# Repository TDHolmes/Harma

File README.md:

# Harma Project

The Harma project first came about when I was talking to my friend and coworker Ben. We are both tinkerers and He used to work as a rework technician, so is quite good at fine pitch soldering. I however, have very shaky hands, so I shy away from anything smaller than an 0805 passive component.

That got me thinking, there are robotic assistants for surgeries, so why not for an over caffeinated tinkerer like myself?

Thus, this project was born. It consists of two major parts:

1. The thing the tinkerer holds on to to control the robot
2. The robotic arms holding:
   * The soldering iron
   * The solder
   * The wire or component

### The Name

Harma comes from the word Härma, which means Mimic in Swedish. A fitting name since the goal of this project is for you to control a robot that mimics your movements in a more precise and filtered way.

## Sub-Components

As stated above, this project consists of two major parts: The thing the user holds to control the robot and the robotic arms itself.

### [Pensel][Pensel Link]

Pensel, or brush/pencil in Swedish, is the device the user interfaces with to control the robotic arms. It is this sub-component that I will first tackle to make the whole system. The design as it stands is as follows:

There will be one unified design to control the iron, solder, and/or wire/components. As such, there must be a generic control methodology built into the Pensel. The Pensel will have:

1. A three position toggle switch for the user to indicate what mode the Pensel is operating in (Soldering iron, solder, or wire/component).
2. One push button to indicate that we are actively moving and want the robot to respond
3. Another push button to do the action supported by the mode. For example:
   * Feed solder
   * Feed wire
   * release component

Further Pensel documentation can be found [here][Pensel Link].

#### The Current design

* Processor
   * STM32F302K8U6
   * ARM® Cortex®-M4
   * 72MHz
   * CAN, I²C, IrDA, LIN, SPI, UART/USART, USB
   * DMA, I²S, POR, PWM, WDT
   * Hardware FPU
* Sensors
   * Combined Accelerometer and Magnetometer (LSM303DLHC) to detect orientation & movement
   * A button to trigger "active" mode
   * An auxiliary button to generate an action
   * A three position switch to indicate the active mode
   * A thumbwheel potentiometer to control sensitivity

### Robotic Arms (Working title)

This section has not been thought through yet. I am currently only focusing on the Pensel sub-component.

[Pensel Link]: https://www.holmesengineering.com/Harma/Pensel "Pensel Sub-Project Page"

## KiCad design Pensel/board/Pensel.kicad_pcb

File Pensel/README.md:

# Pensel

Pensel, or brush/pencil in Swedish, is the device the user interfaces with to control
the robotic arms. It is this sub-component that I will first tackle to make the whole
system. The design as it stands is as follows:

There will be one unified design to control the iron, solder, and/or wire/components.
As such, there must be a generic control methodology built into the Pensel. The
Pensel will have as follows:

1. A three position toggle switch for the user to indicate what mode the Pensel is
operating in (Soldering iron, solder, or wire/component).
2. One push button to indicate that we are actively moving and want the robot to respond
3. Another push button to do the action supported by the mode. For example:
   * Feed solder
   * Feed wire
   * release component

## Hardware Basics

* STM32F302K8U6
  * ARM® Cortex®-M4 (with FPU)
  * I²C, UART/USART, USB, DMA, PWM, WDT
  * 72MHz
* Orientation / motion sensor for orientation and movement detection
  * LSM303DLHC accelerometer and magnetometer for version 1
  * LSM9DS1 accelerometer, magnetometer and gyroscope for version 2

### Pensel v1

![alt text][v1 Board Top]

#### Sensors

Pensel v1 utilized the now obsolete LSM303DLHC, an accelerometer/magnetometer
orientation sensor. I was hoping to achieve absolute orientation sensing with the
gravity vector and magnetic north vector. This is, however, very difficult with
magnetometer data, as it is very noisy and susceptible to local perturbations.

![alt text][v1 Mag Plot]

The accelerometer data, however, looked very promising.

![alt text][v1 Accel Plot]

#### Communication

The communication method was also less than ideal in v1. I utilized a USB to serial
converter chip to provide easy communication to the host, however to accommodate the
high data-rate sensors and have a general purpose report get/set architecture, I
basically re-implemented a USB HID device over serial, which doesn't make much sense.

![alt text][v1 comms]

### Pensel v2

![alt text][v2 Board Top]

Pensel v2 aims to rectify the issues with v1 by using a more robust, in production
accelerometer, magnetometer, and gyroscope sensor, the LSM9DS1. It also will
eliminate the USB to serial converter in favor of a direct USB connection and a
custom HID USB device. It is also my first adventure into four layer boards, which
made routing a dream.

#### Current Progress

I am currently working on getting the USB stack up and working. I found that I
forgot the 1.5k pull-up resistor on the D+ pin of the USB connection, which is
required to indicate device speed and device attachment. I have attached a bodge
wire to the D+ net (luckily I had pads for filter capacitors in case they were
needed) and am working on soldering some 0805 resistors to that line.

## Initial Software Design

Below is an overview of all of the modules in the system. This is only an initial
cut at the system and is subject to change.

![alt text][Software Diagram]

Below is an overview of the control and call structure of the system.

![alt text][Control Diagram]

[Software Diagram]: https://raw.githubusercontent.com/TDHolmes/Harma/master/Pensel/documentation/pictures/Pensel_SoftwareDiagram.png "Overall Pensel software diagram"
[Control Diagram]: https://raw.githubusercontent.com/TDHolmes/Harma/master/Pensel/documentation/pictures/Pensel_ControlHierarchy.png "Pensel control flow"

[v1 Board Top]: https://github.com/TDHolmes/Harma/blob/gh-pages/Pensel/documentation/pictures/Pensel_1_0_top.jpg?raw=true "Pensel v1 - Top"
[v1 Board Bottom]: https://github.com/TDHolmes/Harma/blob/gh-pages/Pensel/documentation/pictures/Pensel_1_0_bottom.jpg?raw=true "Pensel v1 - Bottom"

[v1 Accel Plot]: https://github.com/TDHolmes/Harma/blob/gh-pages/Pensel/Documentation/pictures/P1_HalfRotation_accel.png?raw=true "Accel plot of a half rotation of the unit"
[v1 Mag Plot]: https://github.com/TDHolmes/Harma/blob/gh-pages/Pensel/Documentation/pictures/P1_magRotation.png?raw=true "Magnetometer plot of a full Pensel rotation"
[v1 comms]: https://github.com/TDHolmes/Harma/blob/master/Pensel/Documentation/P1_UART_coms.png?raw=true "Pensel v1 UART packet definition"

[v2 Board Top]: https://github.com/TDHolmes/Harma/blob/master/Pensel/Documentation/pictures/Pensel_v2_Top.jpg?raw=true "Pensel v2 - Top"

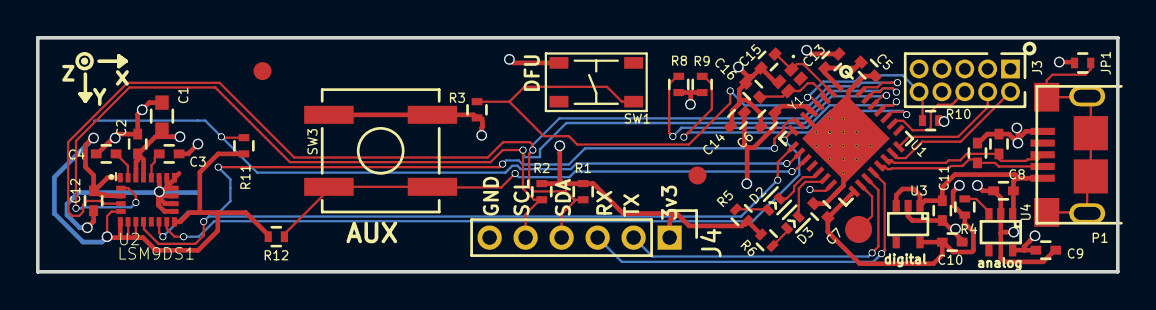
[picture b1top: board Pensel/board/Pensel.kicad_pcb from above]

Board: 4 copper layers, 60.0 x 13.0 mm, 48 parts (1 on the bottom side), 33 nets.

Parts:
C1: 10 uF; C_0603
C2, C4, C6, C7, C12, C13: 0.1 uF; C_0402
C3: 10 nF; C_0402
C5: 4.7 uF; C_0402
C8, C9, C10, C11, C14: 1 uF; C_0402
C15, C16: 8 pF; C_0402
C_NOSTUFF1, C_NOSTUFF2: 0.1 uF; C_0402
D2: LED0; LED_0402
D3: LED1; LED_0402
J1: TEST_1P; Measurement_Point_Round-SMD-Pad_Small
J2, J5: Fiducial; Fiducial_1mm_Dia_2.54mm_Outer_CopperBottom
J3: JTAG; Pin_Header_Straight_2x05_Pitch1.27mm
J4: COMS; Pin_Header_Straight_1x06_Pitch2.00mm
J6, J7: Fiducial; Fiducial_1mm_Dia_2.54mm_Outer_CopperTop
JP1: Jumper; R_0402
P1: USB_PROC; 2013499-1
R1, R2, R3, R4, R8, R9, R10, R11, R12: 4K7; R_0402
R5, R6: 330R; R_0402
SW1: TACT_4.2MM; MF_Switches-TACT4.2MM
SW2: MAIN; SW_SPST_B3SL-1002P
SW3: AUX; SW_SPST_B3SL-1002P
U1: STM32F302x6/8; QFN-32-1EP_5x5mm_Pitch0.5mm
U2: LSM9DS1; PQFN24P43_350X300X102L35X23N
U3: NCP114; SC-70-5
U4: NCP508; SC-70-5
Y1: 24 MHz; OSCSC49P160X120X45-4N

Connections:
+3.3VA: C1.1, C2.1, C6.1, C9.1, C14.1, U1.5, U2.22, U2.23, U4.5
+3V3: C5.1, C7.1, C10.1, C12.1, C13.1, J3.1, J4.1, R1.1, R2.1, R4.2, R5.1, R6.1, R10.1, R11.1, R12.1, SW1.1, U1.1, U1.17, U2.1, U2.3, U2.5, U2.6, U2.7, U2.8, U2.13, U3.5
+5V: C8.1, C11.1, P1.1, U3.1, U3.3, U4.1
/USB+: C_NOSTUFF1.2, P1.3, U1.22
/USB-: C_NOSTUFF2.1, P1.2, U1.21
/test_pin: J1.1, U1.18
AG_INT1: U1.7, U2.11
AG_INT2: U1.8, U2.12
BREV-0: R9.1, U1.27
BREV-1: R8.1, U1.28
BTN_AUX: R12.2, SW3.2, U1.11
BTN_MAIN: R11.2, SW2.2, U1.10
GND: C1.2, C2.2, C3.2, C4.2, C5.2, C6.2, C7.2, C8.2, C9.2, C10.2, C11.2, C12.2, C13.2, C14.2, C15.2, C16.2, C_NOSTUFF1.1, C_NOSTUFF2.2, J3.3, J3.5, J3.9, J4.6, JP1.1, P1.5, R3.2, R8.2, R9.2, SW2.1, SW3.1, U1.6, U1.16, U1.32, U1.33, U2.14, U2.15, U2.16, U2.17, U2.18, U2.19, U2.20, U3.2, U4.2, Y1.2
LED0: D2.1, U1.13
LED1: D3.1, U1.14
M_DRDY: U1.9, U2.9
unnamed: C3.1, U2.21
unnamed: C4.1, U2.24
unnamed: C15.1, U1.2, Y1.1
unnamed: C16.1, U1.3, Y1.3
unnamed: D2.2, R5.2
unnamed: D3.2, R6.2
unnamed: JP1.2, P1.6
unnamed: R3.1, SW1.4, U1.31
unnamed: R4.1, U4.3
RESET_n: J3.10, R10.2, U1.4
SCL: J4.5, R2.2, U1.29, U2.2
SDA: J4.4, R1.2, U1.30, U2.4
SWD-SWCLK: J3.4, U1.24
SWD-SWO: J3.6, U1.26
SWDIO: J3.2, U1.23
UART_RX: J4.3, U1.20
UART_TX: J4.2, U1.19

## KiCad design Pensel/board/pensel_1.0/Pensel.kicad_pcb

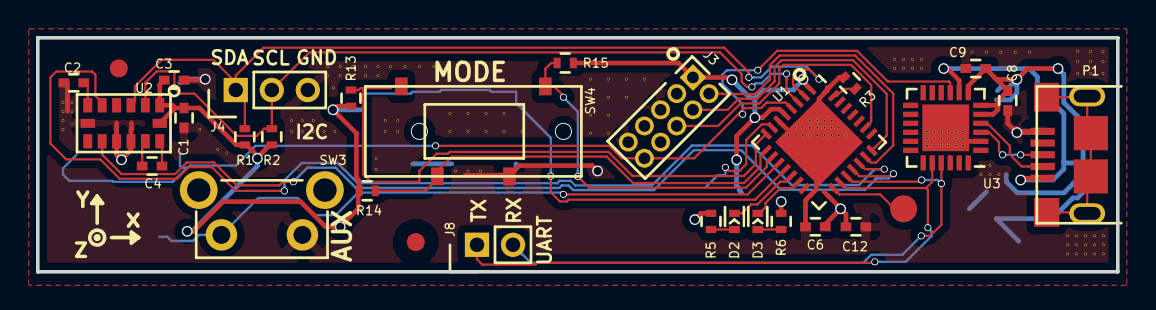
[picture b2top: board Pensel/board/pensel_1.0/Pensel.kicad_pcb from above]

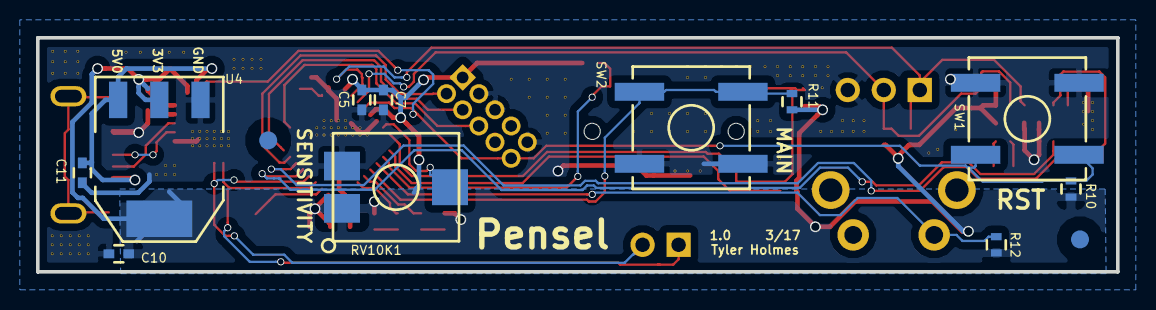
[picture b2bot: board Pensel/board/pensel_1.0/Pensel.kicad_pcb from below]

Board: 2 copper layers, 60.0 x 13.0 mm, 43 parts (11 on the bottom side), 30 nets.

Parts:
C1, C2, C5, C8: 4.7 uF; C_0402
C3, C6, C9, C12: 0.1 uF; C_0402
C4: 0.22 uF; C_0402
C7, C10, C11: 1 uF; C_0402
D2: LED0; LED_0402
D3: LED1; LED_0402
J1: TEST_1P; Measurement_Point_Round-SMD-Pad_Small
J2, J5: Fiducial; Fiducial_1mm_Dia_2.54mm_Outer_CopperBottom
J3: JTAG; Pin_Header_Straight_2x05_Pitch1.27mm
J4: I2C; Pin_Header_Straight_1x03_Pitch2.00mm
J6, J7: Fiducial; Fiducial_1mm_Dia_2.54mm_Outer_CopperTop
J8: UART; Pin_Header_Straight_1x02_Pitch2.00mm
P1: USB_PROC; 2013499-1
R1, R2, R3, R10, R11, R12, R13, R14, R15: 4K7; R_0402
R5, R6: 330R; R_0402
RV10K1: THUMBWHEEL; ST-4
SW1: RST; SW_SPST_B3SL-1002P
SW2: MAIN; SW_SPST_B3SL-1002P
SW3: AUX; SW_Tactile_SPST_Angled
SW4: MODE_SEL; CL-SB-13B-01
U1: STM32F302x6/8; QFN-32-1EP_5x5mm_Pitch0.5mm
U2: LSM303DLHC; LGA_14L_3mm_5mm
U3: CP2102N-A01-GQFN24; QFN-24-1EP_4x4mm_Pitch0.5mm
U4: AP111733; SOT-223

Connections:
+3V3: C1.1, C3.1, C5.1, C6.1, C7.1, C8.1, C9.1, C10.1, C12.1, J3.1, R1.1, R2.1, R5.1, R6.1, R10.1, R11.1, R12.1, R13.1, R14.1, R15.2, RV10K1.1, U1.1, U1.5, U1.17, U2.1, U2.14, U3.5, U3.6, U3.7, U4.2, U4.4
+5V: C11.1, P1.1, U3.8, U4.3
BTN_AUX: R12.2, SW3.2, U1.11
BTN_MAIN: R11.2, SW2.2, U1.12
DBG_UART_RX: J8.2, U1.20, U3.21
DBG_UART_TX: J8.1, U1.19, U3.20
GND: C1.2, C2.2, C3.2, C5.2, C6.2, C7.2, C8.2, C9.2, C10.2, C11.2, C12.2, J3.3, J3.5, J3.9, J4.3, P1.5, R3.2, RV10K1.3, SW1.1, SW2.1, SW3.1, SW4.3, U1.6, U1.16, U1.32, U1.33, U2.7, U2.10, U2.11, U3.2, U3.25, U4.1
LED0: D2.1, U1.13
LED1: D3.1, U1.14
MODE_0: R13.2, SW4.1, U1.8
MODE_1: R14.2, SW4.2, U1.9
MODE_2: R15.1, SW4.4, U1.10
unnamed: C2.1, U2.6
unnamed: C4.1, U2.13
unnamed: C4.2, U2.12
unnamed: D2.2, R5.2
unnamed: D3.2, R6.2
unnamed: J1.1, U1.18
unnamed: P1.2, U3.4
unnamed: P1.3, U3.3
unnamed: R3.1, U1.31
RESET_n: J3.10, R10.2, SW1.2, U1.4, U3.9
SCL: J4.2, R2.2, U1.3, U2.2
SDA: J4.1, R1.2, U1.2, U2.3
SEN_DRDY: U1.21, U2.9
SEN_INT1: U1.22, U2.5
SWD-SWCLK: J3.4, U1.24
SWD-SWO: J3.6, U1.26
SWDIO: J3.2, U1.23
THUMBWHEEL: RV10K1.2, U1.7

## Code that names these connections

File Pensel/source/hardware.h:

#ifndef _HARDWARE_H_
#define _HARDWARE_H_


#include "stm32f3xx.h"

// Sensor stuff
#define SENSOR_PORT (GPIOA)
#define SENSOR_DRDY (GPIO_PIN_11)
#define SENSOR_INT  (GPIO_PIN_12)

// LED / exposed pad stuff
#define LED_PORT   (GPIOA)
#define LED_0      (GPIO_PIN_6)
#define LED_1      (GPIO_PIN_7)
#define EXTRA_GPIO (GPIO_PIN_8)

// Button & switch stuff
#define SWITCH_BUTTON_PORT (GPIOA)
#define BUTTON_MAIN        (GPIO_PIN_5)
#define BUTTON_AUX         (GPIO_PIN_4)
#define SWITCH_0           (GPIO_PIN_1)
#define SWITCH_1           (GPIO_PIN_2)
#define SWITCH_2           (GPIO_PIN_3)

// Thumbwheel
#define THUMBWHEEL_PORT (GPIOA)
#define THUMBWHEEL      (GPIO_PIN_0)

// I2C
#define I2C_PORT    (GPIOF)
#define I2C_SDA     (GPIO_PIN_0)
#define I2C_SCL     (GPIO_PIN_1)

// UART
#define UART_PORT   (GPIOA)
#define UART_RX     (GPIO_PIN_10)
#define UART_TX     (GPIO_PIN_9)


// Public function definitions
void SystemClock_Config(void);
void configure_pins(void);

void LED_toggle(uint16_t LED);
void LED_set(uint16_t LED, uint8_t value);


#endif /* _HARDWARE_H_ */

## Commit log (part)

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2017-03-11 adding in sub-folder for Pensel sub component
2017-03-12 adding in PinAllocations spreadsheet
2017-03-12 First revision of pinout complete
2017-03-13 fixing formatting issues and adding some more inof
2017-03-13 stubbing out I2C functions required
2017-03-13 adding in common header for ret_t retval enumeration
2017-03-13 adding explicit cast to int16_t
2017-03-15 Initial schematic placement
2017-03-15 Placement of major components
2017-03-15 most of the major wiring
2017-03-16 adding in processor ref manual
2017-03-16 adding STM HAL files
2017-03-19 moved datasheets into folder and added FTDI and accel
2017-03-26 adding .kicad_pcb-bak to gitignore
2017-03-26 gerber output of first complete route
2017-03-26 fixing output folder and contents for gerber files
2017-04-02 switched to LSM303DLHC accel and gyro only and did first cut at ull route
2017-04-08 final modifications and gerber export for v1_0 sent to macrofab
2017-04-22 removing STM_drivers folder in favor of a peared down drivers folder
2017-04-22 initial cut at UART using HAL
2017-04-22 adding required libraries
2017-04-22 adding linker file
2017-04-22 adding in a hardware file for hardware specific functions
2017-04-22 fixing up my files so they're HAL complient
2017-04-22 first successful build of the project
2017-04-22 added a UART_isReady() function to see if UART tx is busy
2017-04-24 adding stupid catchall RET_GEN_ERR to ret_t type
2017-04-29 adding queues to the sensor for easy getting from app code
2017-04-29 adding -g to release flags so we can debug
2017-04-29 adding interrupt for sensor and configuring priorities
2017-04-29 adding .elf files to ignor
2017-04-29 adding helloWorld UART in main loop and an implementation of the HAL_IncTick function for 1ms ISR to call other functions that need periodic updating
2017-04-30 switching CRLF to LF
2017-04-30 switching to LF to CRLF
2017-05-01 implementing the interrupt prioritization as well as documenting it
2017-05-01 fixing linker script name and adding a check if folders exist. if not, make it
2017-05-05 the start of reports structure
2017-05-05 moving queue_t to queue.h
2017-05-05 adding a peakChar function
2017-05-06 getting UART to work properly
2017-05-06 fixing up hal config file
2017-05-06 adding GDB startup script and moving build script to scripts folder
2017-05-06 some debug main loop things for board bringup
2017-05-14 removing unused code for different chip
2017-05-14 adding parser scripts for UART data and recorded data for offline playback
2017-05-14 Making I2C work
2017-05-14 Switching SystemClock_Config to a different example
2017-05-14 making fatal_error_handler print file and line number of error and adding some return types
2017-05-14 cleaning up and making LSM303DLHC code work
2017-05-15 fimrware folder re-organize
2017-05-17 adding more description to the GDB startup python script
2017-05-17 adding in normalization code and switching accel and mag datatypes to float
2017-05-17 adding functions to toggle the extra timing GPIO
2017-05-17 removing the deleted cli.c/h files
2017-05-21 adding tests for newqueue and improving other tests
2017-05-21 adding/fixing doxygen comments
2017-05-21 fixing build script per reorg and made it prettier
2017-05-21 switching scripts over to floating point
2017-05-21 increasing heap size and adding some optional linker flags
2017-05-21 switching to reflect changes in report module and LSM sensor packet changes
2017-05-22 documenting UART methods and cleaning up
2017-05-22 slight adjustments
2017-05-22 adding more queue tests
2017-05-25 Adding watchdog support
2017-06-03 Adding timeouts and magic numbers
    Reports will now timeout after "RPT_TIMEOUT" time.
    Reports also must now start with two magic bytes, 0xBE and 0xEF to signify
    the start of a report to avoid corrupt reports and getting out of sync.
    :
2017-06-03 addinng UNUSED_PARAM macro and RET_NOMEM_ERR when malloc is involved
2017-06-03 interrupt handlers now end with _ISR
2017-06-03 removing .h files from add_executable source list
2017-06-03 adding FIR support as well as some coefficients
2017-06-03 initial add for quanternion support
2017-06-03 initial add of the orientation module
    This module will be responsible for:
    1. Calculating gravity vector orientation
    2. Calculating North vector orientation
    3. Using (1) and (2) to calculate Pensel's orientation
2017-06-03 Adding a draw.io UML diagram of an overview of the blocks of the system
    This is a great high level visualization of low level drivers leading up to
    high level blocks that crank on the data and do the real work.
2017-06-03 updating project info as some things have changed
2017-06-04 Moving HAL specific configuration code to DriverConf folder
    This is mainly to avoid getting all of the HAL configuration code included in the
    doxygen firmware documentation. Super annoying... the PDF becomes 1300 pages long
    with all of the driver documentation!
2017-06-04 adding better support for doxygen PDF generation
2017-06-04 removing unnecessary definition
2017-06-04 making orientation compile in
2017-06-04 changing to signed datatypes in two for loops as we have a >= 0 conditional
2017-06-12 adding static declarations where applicable and adding some docs
2017-06-12 initial layout of the gh-pages
2017-06-12 fixing up documentation
2017-06-12 fixing format error
2017-06-12 adding firmware documentation
2017-06-12 fixing format
2017-06-12 making Pensel documentation link absolute
2017-06-12 adding http redirect
2017-06-25 making LED_set make logical sense given the active low LED config and fixing hardware dependencies
2017-06-25 minor cleanup and tweaking temperature report
2017-06-25 adding python script to send reports
2017-06-25 adding frame_num to accel and mag packets
2017-06-25 some more minor reports
2017-06-25 updated pensel docs with pixtures
2017-06-25 consolidating and renaming the coefficients files
2017-06-25 cleaning up FIR and added a testcase for the FIR filter
2017-06-26 adding schematic PDF and timing analysis pictures
2017-06-26 fixing normalization of vector
2017-06-26 fixing timing pin declaration
2017-06-26 getting plot sensor data script to work with new reports
2017-06-26 consolidating FIR_coefficients filename change
2017-06-26 Changing mag sensitivity
2017-07-02 Switching accel & mag queues to hold raw, then normalize on get packet
2017-07-02 Adding a queue init method to (re)initialize the queue admin to zero
2017-07-02 Added some report constants to common and a critical errors structure.
2017-07-02 changing to reflect packet raw v norm change
2017-07-02 Initial add of the pensel software written in Rust.
2017-07-02 name change to reflect LSM303DLHC raw v norm packets.
2017-07-02 semicolons....
2017-07-03 Pulling I2C logic out of the pin ISR
2017-07-03 Better I2C error handling and comments
2017-07-03 line endings
2017-07-04 restructuring reporting methods to support more general packet receiving
    Now we send a two magic bytes to indicate we are sending a packet up to
    host, so we can support input reports as well as control reports in the
    same manor becuase we don't know when to expect input reports.
2017-07-04 switching to stream by default
2017-07-04 adding a watchdog capture flag to capture the unit after watchdog.
2017-07-04 refactored UART TX ready blocking to have a timeout
2017-07-06 Switching to use #pragma once over ifdef protections in headers
2017-07-10 Initial calibration support code
2017-07-10 updating firmware documentation
2017-07-11 Adding cal to compile list
2017-07-11 switching to using quanternion_vect_t from old quanternion_vector_t
2017-07-11 adding doxygen to default_cal.h
2017-07-11 adding some defines to .clang_complete
2017-07-11 Initial calibration script. Doesn't generate full blob yet
2017-07-15 Adding flash items to the compiler file
2017-07-15 switching penselinputs to having a threadded listener
2017-07-15 Fixing cal script
2017-07-15 putting cal reports in and adding a critical errors getter
2017-07-15 Adding flag to control normalization of packets (gain wise)
2017-07-15 Changing default ODR's on accel and mag to avoid overwrites
    It seems the DRDY pin is tied to magnetometer data only. Thus, I've set
    mag ODR to 220 Hz and accel to 200 Hz so we should never miss an accel
    packet.
2017-07-22 Refactored scripts for stability
    We now only ever get data from pensel in the thread context of listener.
    Before, input streaming used the listener and report setters grabbed
    data itself. This caused major stability issues...
2017-07-22 fixing queue unit test
2017-07-22 add min / max macro definitions if not already defined
2017-07-22 minor cleanup
2017-08-05 making the max RX and TX sizes available in the header
2017-08-05 implementing some orientation things
2017-08-05 adding checksum & non-blocking TX, getting critical errors from extern
    Haven't tested the checksum or non-blocking TX yet
2017-08-05 Look at how noisy that magnetometer data is. woah.
2017-12-24 many good script changes
2017-12-24 small changes to the schematic & board
2017-12-26 adding python3 folder ignore
2017-12-26 fixin up some scriptsss
2017-12-26 some better report logic
2017-12-26 misc cleanup and adding datasheet
2017-12-26 changing transaction definition
    now all reports, both ways, require [DE AD BE EF] header to indicate a
    start to avoid false starts.
2017-12-28 switching to a full "DEADBEEF" header to prevent incorrect starts
2017-12-29 making newqueue compatible with > 255 elements
2017-12-29 Adding newqueue to the build list
2017-12-29 always send the critical error message
2017-12-29 Adding input report queueing
2017-12-29 increasing RX / TX buffer sizes so we don't need multiple transactions
    This drastically increases performance and makes it so we don't drop
    bytes!
2018-01-01 implement multiple pop / push at a time
2018-01-01 switching to new newqueue syntax
2018-01-02 fix some newqueue logic
2018-01-02 bump UART up in speed a bit to avoid packet loss
2018-01-02 Add a short git tag to the pensel versoning
2018-01-02 No longer do convoluted queueing of reports.
2018-01-02 add a dummy definition of a compiler defined GIT_TAG_SHORT def
2018-01-08 adding some algs and a visualizer for prototyping those algs
2018-01-14 algs dev, playback support, object cleanup
2018-01-21 fix some changed syntax and add FFT plotting
2018-01-21 add a new window in the visualizer
2018-01-21 initial schematic changfes
2018-02-19 Many changes supporting board revision 2.0
2018-02-22 first time fully routed and placed v2
2018-02-24 No need to keep all of these old versions of pensel HW around
2018-02-24 ignore gerber file output
2018-02-25 reorganize pins, add oscillator to support USB
2018-03-19 finish up board; move around some docs
2018-03-19 Initial restructure
    This restructure is to better support multi-board targeting and hopefully
    allow for better code structure
2018-03-19 adding STM32 USB library
2018-03-19 It actually builds!
2018-03-28 initial example I found using libusb
2018-04-21 allow different build targets
2018-04-21 support for unittests build
2018-04-21 ifdef around v1 specific code
2018-04-22 adding final v2 schematic
2018-04-22 add v1 schematic
2018-04-22 reconfigure I2C and other peripherals for v2
2018-04-22 point to the correct .elf in the build size and usage subcommands
2018-04-22 initialize UART and cleanup some LSM stuff
2018-04-28 add basic scheduler
2018-05-01 Create LICENSE
2018-05-19 small changes
2018-05-19 USB datapair protection datasheet. Definitely should've used this
2018-05-19 updated ignores for GH pages
2018-05-19 further refinements
2018-05-19 Adding some communication arch documentation
2018-05-20 v2 pictures
2018-05-20 Simplify hardware basics section
2018-05-24 Initial creation of LSM9DS1 driver code
2018-05-27 Reformatting descriptor comment structure. No real code change
2018-05-27 Some more cleanup
2018-07-13 Many small refactors; USB serial works!
2018-07-14 refactor some usb; break CDC stuff into it's own module
2018-07-14 re-enable the scheulder stuffz
2018-07-14 cleanup main a bit
2018-07-15 initialize state, use correct error handler function
2018-07-15 extra space
2018-07-15 initial add of .clang-format file for defining project style rules
2018-07-16 Fix I2C init stuff
2018-07-16 fix build script default arg to be valid
2018-08-05 add logging module
2018-08-12 Many changes:
    - Doxygen updates
    - Docstring updates (everywhere)
    - USB HID files
    - Queue up gyro/mag/accel packets
    - Accessor methods for those packets
    - Control reports to get said packets
2018-08-12 more clang-format changes; delete defunct UART reports
2018-11-24 refactored unit testing scheme
    moved to a more scalable cmake build setup. Also added a basic
    test for the logging module.
2018-11-24 some sort of include shuffling made this include necessary
2018-11-24 minor logging changes
